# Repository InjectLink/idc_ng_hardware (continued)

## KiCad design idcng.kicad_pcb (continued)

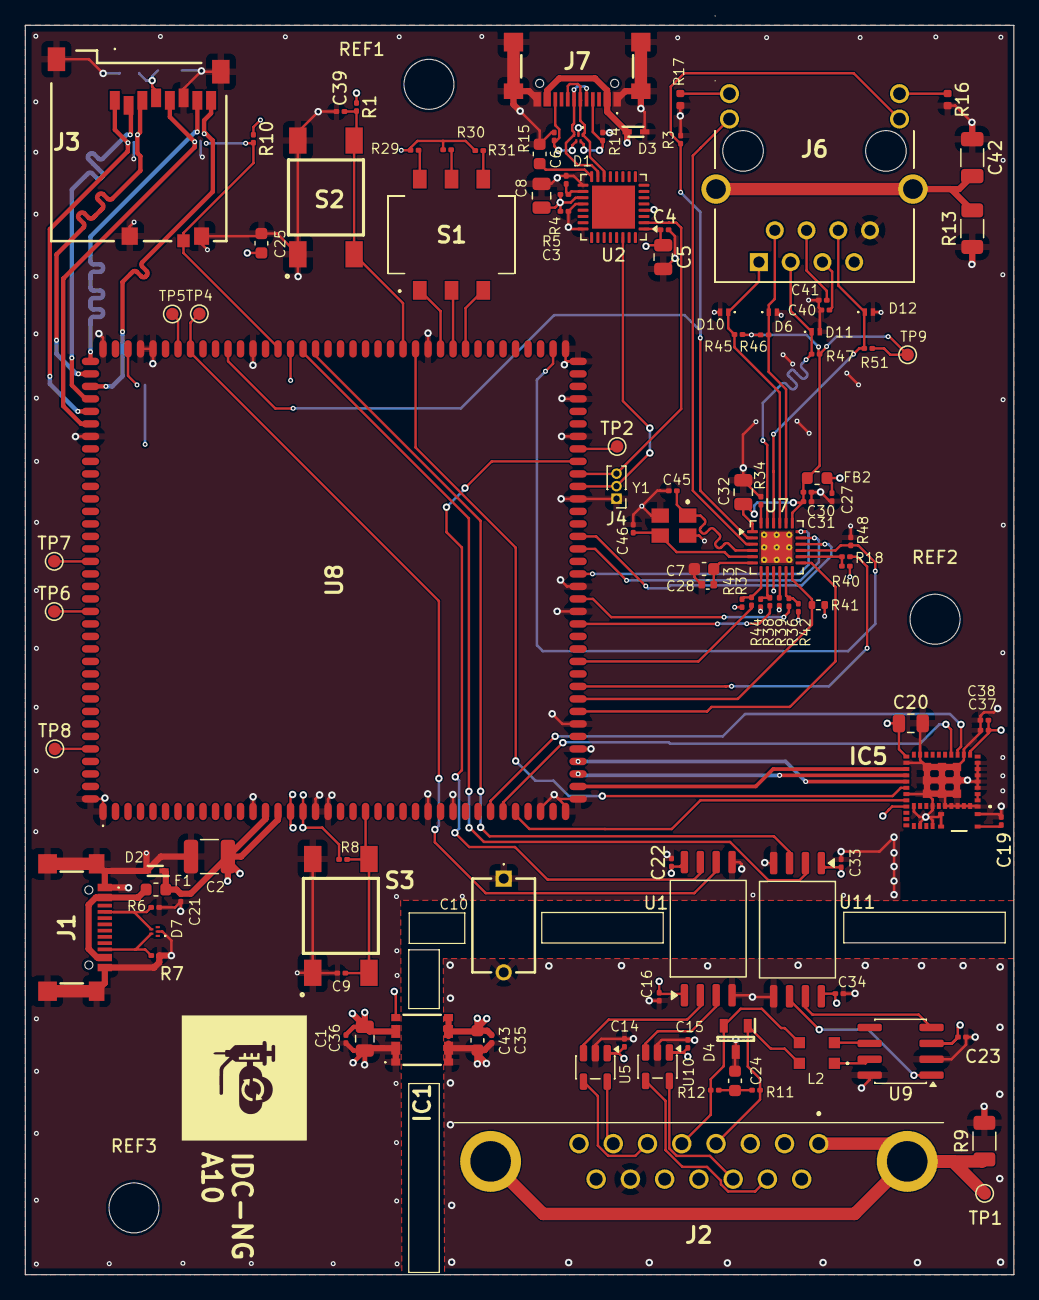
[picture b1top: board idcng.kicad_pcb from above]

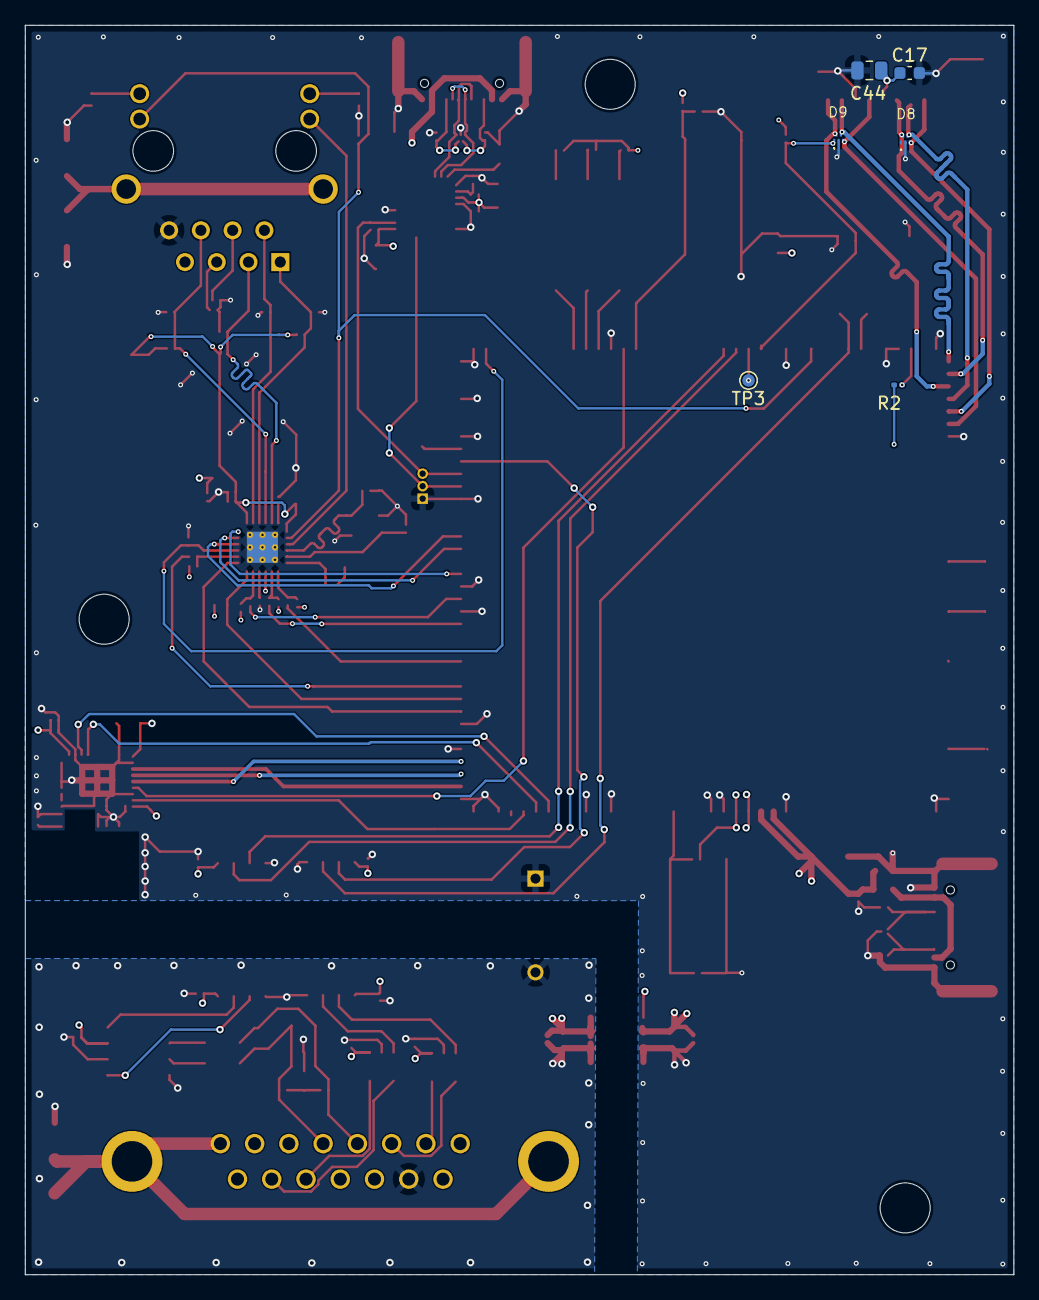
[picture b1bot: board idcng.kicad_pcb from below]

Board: 4 copper layers, 79.1 x 99.9 mm, 122 parts (6 on the bottom side), 97 nets.

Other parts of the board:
C25: 1u/16V; C_0603_1608Metric
R40: 10k; R_0201_0603Metric
REF1, REF2, REF3: MountingHole_4mm

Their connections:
+3V3: C25.1, R40.1; also elsewhere on the board
GND: C25.2; also elsewhere on the board
unnamed 59: R40.2; also elsewhere on the board

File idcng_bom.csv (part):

Reference;Qty;Value;DNP;Exclude from BOM;Exclude from Board;Footprint;Datasheet;Mouser Price/Stock;Pricep1;Pricep10;Pricep100
C1,C14,C15,C16,C18,C21,C22,C23,C27,C29,C30,C31,C33,C34,C35,C37,C38,C39,C40,C41;20;100n/16V;;;;Capacitor_SMD:C_0201_0603Metric;https://www.yuden.co.jp/productdata/catalog/mlcc02_e.pdf;https://www.mouser.fr/ProductDetail/TAIYO-YUDEN/EMK063BJ104K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;0,086;0,042;0,03
C2;1;47u/10V;;;;Capacitor_SMD:C_1210_3225Metric;https://www.mouser.com/catalog/specsheets/TAIYO%20YUDEN_03-0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;https://www.mouser.fr/ProductDetail/TAIYO-YUDEN/MSASE32MSB54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;0,774;0,517;0,372
C17,C25,C26;3;1u/16V;;;;Capacitor_SMD:C_0603_1608Metric;https://www.mouser.fr/datasheet/3/508/1/upy-gphc_x5r_4v-to-50v.pdf;https://www.mouser.fr/ProductDetail/YAGEO/CC0603KRX5R6BB105?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;0,086;0,032;0,028
C19;1;0.9p/50V;;;;Capacitor_SMD:C_0201_0603Metric;https://www.mouser.fr/datasheet/3/76/1/GCQ0335C1HR90WB01-01A.pdf;https://www.mouser.fr/ProductDetail/Murata-Electronics/GCQ03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;0,155;0,09;0,055
C20,C32,C36,C44;4;10u/16V;;;;Capacitor_SMD:C_0805_2012Metric;https://www.samsungsem.com/resources/file/global/support/pro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;https://www.mouser.fr/ProductDetail/Samsung-Electro-Mechanic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;0,086;0,03;0,026
C24;1;4.7n/100V;;;;Capacitor_SMD:C_0603_1608Metric;https://datasheets.kyocera-avx.com/AutoMLCCKAM.pdf;https://www.mouser.fr/ProductDetail/KYOCERA-AVX/KAM15AR72A47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;0,086;0,05;0,03
C28;1;470p/16V;;;;Capacitor_SMD:C_0402_1005Metric;https://www.mouser.fr/datasheet/3/508/1/KEM_C1007_X8R_ULTRA_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;https://www.mouser.fr/ProductDetail/KEMET/C0402C471J4HACAUTO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;0,095;0,055;0,034
C42;1;1n/2kV;;;;Capacitor_SMD:C_1206_3216Metric;https://www.mouser.fr/datasheet/3/317/1/Middle_and_High_Volt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;https://www.mouser.fr/ProductDetail/Walsin/1206B102M202CT?qs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;0,108;0,039;0,033
C43;1;22u/16V;;;;Capacitor_SMD:C_0603_1608Metric;https://www.mouser.fr/datasheet/3/76/1/ZRB18AR61C226ME01-01A.pdf;https://www.mouser.fr/ProductDetail/Murata-Electronics/ZRB18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;0,378;0,247;0,152
C45,C46;2;22p/50V;;;;Capacitor_SMD:C_0201_0603Metric;https://www.mouser.fr/datasheet/3/76/1/GCQ0335C1H220JB01-01A.pdf;https://www.mouser.fr/ProductDetail/Murata-Electronics/GCQ03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;0,103;0,041;0,024
D2;1;UCLAMP0501H.TCT;;;;SODFL1608X70N;https://datasheet.datasheetarchive.com/originals/distributor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;https://www.mouser.fr/ProductDetail/Semtech/UCLAMP0501H.TCT?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;0,808;0,509;0,333
D4;1;DESD2CAN2SOQ-7;;;;SOT96P240X110-3N;https://www.mouser.fr/datasheet/3/175/1/DESD2CAN2SOQ.pdf;https://www.mouser.fr/ProductDetail/Diodes-Incorporated/DESD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;0,249;0,138;0,114
D5;1;150202M153130;;;;150202M153130;https://www.we-online.com/components/products/datasheet/1502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;https://www.mouser.fr/ProductDetail/Wurth-Elektronik/150202M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;0,473;0,43;0,387
F1;1;SF-0603F250-2;;;;Fuse:Fuse_0603_1608Metric;https://www.mouser.fr/datasheet/3/40/1/sf0603f.pdf;https://www.mouser.fr/ProductDetail/Bourns/SF-0603F250-2?qs=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;0,525;0,438;0,307
FB2;1;BBGK00160808601Y00;;;;Inductor_SMD:L_0603_1608Metric;https://www.mouser.fr/datasheet/3/203/1/BBGK_Series.pdf;https://www.mouser.fr/ProductDetail/Pulse-Electronics/BBGK00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;0,086;0,034;0,024
IC1;1;MIE1W0505BGLVH-3R-P;;;;MIE1W0505BGLVH3RP;https://www.mouser.de/datasheet/2/277/MIE1W0505BGLVH-3392698.pdf;https://www.mouser.co.uk/ProductDetail/Monolithic-Power-Syst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;1,57;1,54;1,46
IC4;1;EMIF06-HSD03F3;;;;EMIF06HSD03F3;https://www.st.com/resource/en/datasheet/emif06-hsd03f3.pdf;https://www.mouser.fr/ProductDetail/STMicroelectronics/EMIF0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;0,439;0,368;0,31
IC5;1;WFM200S022XNA3;;;;WFM200S022XNA3;https://www.mouser.fr/datasheet/3/340/1/wfm200_datasheet.pdf;https://www.mouser.fr/ProductDetail/Silicon-Labs/WFM200S022X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;9,6;8,34;7,31
J1;1;USB4216-03-A;;;;USB421603A;https://www.mouser.fr/datasheet/3/1507/1/usb4216.pdf;https://www.mouser.fr/ProductDetail/GCT/USB4216-03-A?qs=Tc%2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;0,619;0,539;0,445
J2;1;5747845-6;;;;57478456;https://www.te.com/commerce/DocumentDelivery/DDEController?A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;https://www.mouser.fr/ProductDetail/TE-Connectivity/5747845-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;4,52;4,19;3,46
J3;1;MEM2052-00-195-00-A;;;;MEM20520019500A;https://gct.co/files/drawings/MEM2052.pdf;https://www.mouser.fr/ProductDetail/GCT/MEM2052-00-195-00-A?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;0,955;0,777;0,634
J4;1;Conn_01x03_Pin;;;;Connector_PinHeader_1.00mm:PinHeader_1x03_P1.00mm_Vertical;~;;;;
J5;1;SS-90000-009;;;;SS90000009;https://www.belfuse.com/resources/drawings/stewartconnector/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;https://www.mouser.fr/ProductDetail/Stewart-Connector-Bel/SS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;1,26;1,08;0,894
L2;1;ACE1V3225-201-R;;;;ACE1V3225201R;https://www.eaton.com/content/dam/eaton/products/electronic-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;https://www.mouser.fr/ProductDetail/Eaton-Electronics/ACE1V3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;0,593;0,513;0,413
R1,R39,R40,R41,R42,R43,R44,R48;8;10k;;;;Resistor_SMD:R_0201_0603Metric;https://www.vishay.com/doc?20131;https://www.mouser.fr/ProductDetail/Vishay/CRCW020110K0JNEDA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;0,086;0,023;0,011
R2,R10,R32,R33;4;47k;;;;Resistor_SMD:R_0201_0603Metric;https://www.vishay.com/doc?20131;https://www.mouser.fr/ProductDetail/Vishay/CRCW020147K0FNEDA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;0,095;0,028;0,013
R6,R7;2;5.1k;;;;Resistor_SMD:R_0201_0603Metric;https://www.mouser.fr/datasheet/3/508/1/PYu-AF_51_RoHS_L_9.pdf;https://www.mouser.fr/ProductDetail/YAGEO/AF0201FR-075K1L?qs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;0,086;0,018;0,015
R8,R9;2;75;;;;Resistor_SMD:R_0402_1005Metric;https://industrial.panasonic.com/cdbs/www-data/pdf/RDA0000/A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;https://www.mouser.fr/ProductDetail/Panasonic/ERJ-2GEJ750X?q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;0,086;0,014;0,008
R11,R12;2;60;;;;Resistor_SMD:R_0201_0603Metric;https://www.koaspeer.com/pdfs/RK73-RT.pdf;https://www.mouser.fr/ProductDetail/KOA-Speer/RK73H1HRTTCM60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;0,161;0,079;0,046
R13;1;1M;;;;Resistor_SMD:R_1206_3216Metric;https://www.seielect.com/catalog/SEI-RVCU.pdf;https://www.mouser.fr/ProductDetail/SEI-Stackpole/RVCU1206FT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;0,163;0,084;0,048
R29,R30,R31;3;1k;;;;Resistor_SMD:R_0201_0603Metric;https://www.vishay.com/doc?20131;https://www.mouser.fr/ProductDetail/Vishay/CRCW02011K00JNEDA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;0,086;0,023;0,011
R34;1;12.1k;;;;Resistor_SMD:R_0201_0603Metric;https://industrial.panasonic.com/cdbs/www-data/pdf/RDA0000/A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;https://www.mouser.fr/ProductDetail/Panasonic/ERJ-1GNF1212C?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;0,086;0,022;0,012
R35;1;DNP;;;;Resistor_SMD:R_0201_0603Metric;https://www.mouser.fr/datasheet/3/40/1/cr.pdf;https://www.mouser.fr/ProductDetail/Bourns/CR0201-JW-220GLF?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;0,086;0,009;0,007
R36,R37,R38;3;33;;;;Resistor_SMD:R_0201_0603Metric;https://www.mouser.fr/datasheet/3/40/1/cr.pdf;https://www.mouser.fr/ProductDetail/Bourns/CR0201-JW-330GLF?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;0,086;0,012;0,006
R45,R46,R47,R51;4;49.9;;;;Resistor_SMD:R_0201_0603Metric;https://industrial.panasonic.com/cdbs/www-data/pdf/RDA0000/A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;https://www.mouser.fr/ProductDetail/Panasonic/ERJ-1GNF49R9C?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;0,086;0,022;0,012
R49;1;470;;;;Resistor_SMD:R_0402_1005Metric;https://industrial.panasonic.com/cdbs/www-data/pdf/RDA0000/A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;https://www.mouser.fr/ProductDetail/Panasonic/ERJ-2RKF4700X?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;0,095;0,016;0,009
R50;1;470;;;;Inductor_SMD:L_0402_1005Metric;https://industrial.panasonic.com/cdbs/www-data/pdf/RDA0000/A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;https://www.mouser.fr/ProductDetail/Panasonic/ERJ-2RKF4700X?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;0,095;0,016;0,009
S1;1;DS04-254-2-03BK-SMT;;;;DS04254203BKSMT;https://www.sameskydevices.com/product/resource/ds04-254-smt.pdf;https://www.mouser.fr/ProductDetail/Same-Sky/DS04-254-2-03BK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;0,533;0,46;0,388
S2;1;FSM4JSMATR;;;;FSM4JSMATR;https://www.te.com/commerce/DocumentDelivery/DDEController?A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;https://www.mouser.fr/ProductDetail/TE-Connectivity-Alcoswit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;0,267;0,227;0,194
T1;1;ALANS100X1-2F30DT;;;;ALANS100X12F30DT;https://www.digikey.ph/en/products/detail/abracon-llc/ALANS1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;https://www.mouser.fr/ProductDetail/ABRACON/ALANS100X1-2F30D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;2,07;1,74;1,48
TP1,TP2,TP3,TP4,TP5,TP6,TP7,TP8;8;TestPoint;;;;TestPoint:TestPoint_Pad_D1.0mm;~;;;;
U1;1;18012015421H;;;;Package_SO:SOIC-8_7.5x5.85mm_P1.27mm;https://www.we-online.com/components/products/datasheet/1801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;https://www.mouser.fr/ProductDetail/Wurth-Elektronik/1801201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;1,2;1,15;1,08
U5,U10;2;XR33180ESBTR;;;;Package_TO_SOT_SMD:TSOT-23-5;https://www.maxlinear.com/ds/XR33180_XR33181_XR33183_XR33184.pdf;https://www.mouser.fr/ProductDetail/MaxLinear/XR33180ESBTR?q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;0,894;0,644;0,513
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
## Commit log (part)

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2025-12-01 antenna review
2025-12-01 ground plane on top and bottom. via stitching
2025-12-02 Avoid via in pads
2025-12-02 cleanup
2026-01-16 fix: usb uart reverse support for usb-c
    - Fix usb-c reverse support for data link usb uart
2026-02-16 fix: ethernet clock inversion
    - Fix ethernet clock inversion and mdint for LED activity
2026-02-16 led: remove rgb leb
    - Remove RGB LED (wt I2C controller)
